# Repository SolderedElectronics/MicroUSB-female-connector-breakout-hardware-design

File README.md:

# MicroUSB female connector breakout Hardware Design

## About the Product

|  |
| :----------------------------------------------------------: |
| [Buy MicroUSB female connector breakout](https://www.solde.red/333010) |

The MicroUSB is still everywhere around us, even though it’s slowly being replaced with USB Type-C. We’re sure you wanted to add it to your electronics projects. We did, too, that’s why we added the MicroUSB female connector breakout board to our roster!

The Micro B USB connector’s GND, ID, D+, D-, and VCC pins are broken out to the plated through-holes.

---

## Repository Contents

This repository contains all design files for MicroUSB female connector breakout, organized as follows:

- **`CAD` folder**: Contains KiCAD design files, including:
  - Schematics
  - PCB layout
  - Panel PCB layout
  - Source 3D files in Fusion360, if any
  - All files are sorted by version with a detailed change log.
- **`OUTPUTS` folder**: Includes all production-ready files, such as:
  - Bill of Materials (BOM) and interactive BOM (iBOM)
  - PDF versions of schematics
  - 3D `.step` file of the board
  - 3D-printable models
  - Gerber files for PCB manufacturing
  - Image of the pinout of the board
  - Product image
  - Compliance, legal and generic sales documents

Refer to the `Change Log` in the CAD folder for details about updates between versions.

---

## Learn More About the Product

Beyond the repository, explore the following resources:

### Soldered Verify

The **Soldered Verify** system ensures every board you purchase from Soldered is fully functional. It also provides access to exclusive test data for your product. To get started, find the unique Soldered Verify ID on your product's packaging and enter the ID on the [Soldered Verify page](https://soldered.com/verify/) to access test results and additional product details.

### Soldered Community

Soldered Community is your go-to place for technical support. Our engineers track and answer all questions posted there, and it’s a great space for the maker community. Get answers to your questions and solutions for your challenges at [Soldered Community](https://soldered.com/community).

### solde.red

solde.red is an ultimate URL shortener and information hub. Access it by typing solde.red/ followed by your product SKU, e.g., [solde.red/333000](https://solde.red/333000), to find getting-started guides, datasheets, open-source hardware and software files, certifications, images, pinouts, and more. Read more about the shortener [here](https://solde.red/info/).

---

## Contributing

Contributions are welcome! Here’s how you can get involved:

- Submit pull requests to enhance the design or fix issues.
- Report bugs or problems by opening an issue.

We encourage community collaboration to make this product even better.

---

## About Soldered

[Soldered for Makers](https://soldered.com) specializes in designing and manufacturing electronic products tailored for enthusiasts, ranging from hobbyists to professionals. Our portfolio includes electronic boards, sensors, and actuators that are widely utilized in fields such as microelectronics, mechatronics, robotics, programming, and IoT. Every product we offer is designed in-house and built upon open-source hardware and software platforms. Proudly certified and manufactured within the European Union, our catalog likely includes the product you need for your project.

We complement these products with comprehensive tutorials and manuals, product descriptions, schematics, programming codes, and project examples. Our round-the-clock [customer and technical support](https://soldered.com/community) is available for all our products, irrespective of the sales channel. Soldered’s success and services reflect our maker community’s unwavering [trust](https://www.trustpilot.com/review/soldered.com), for which we are deeply grateful. Join our community and create using Soldered products.

---

## License

All Soldered open-source hardware (OSH) is under The TAPR Open Hardware License. Read more in the LICENSE file located in this repository.

**Disclaimer:**

No warranty - all designs in this repository are distributed in the hope that they will be useful, but without any warranty. They are provided "AS IS", therefore without warranty of any kind, either expressed or implied. The entire quality and performance of what you do with the contents of this repository are your responsibility. In no event Soldered Electronics will be liable for your damages, or losses, including any general, special, incidental, or consequential damage arising out of the use or inability to use the contents of this repository. 

---

## Have fun!

Thank you for your support from your fellow makers at Soldered Electronics.

Happy Making!

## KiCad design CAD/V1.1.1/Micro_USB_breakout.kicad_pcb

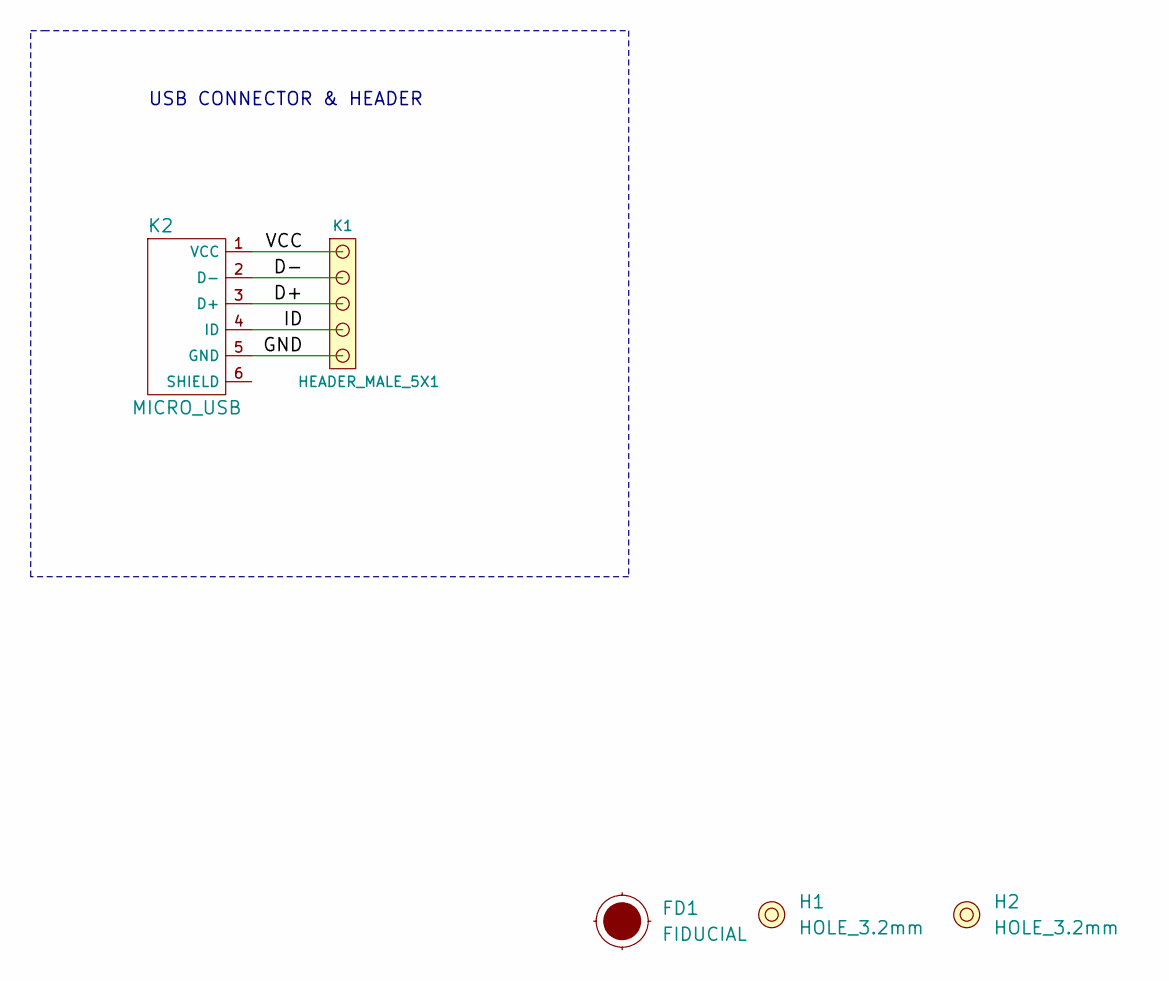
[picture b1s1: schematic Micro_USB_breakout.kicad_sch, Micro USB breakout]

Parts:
FD1: FIDUCIAL; FIDUCIAL_23
H1, H2: HOLE_3.2mm
K1: HEADER_MALE_5X1
K2: MICRO_USB

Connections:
/D+: K1.3, K2.3 (D+)
/D-: K1.4, K2.2 (D-)
/GND: K1.1, K2.5 (GND)
/ID: K1.2, K2.4 (ID)
/VCC: K1.5, K2.1 (VCC)

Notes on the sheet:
USB CONNECTOR & HEADER

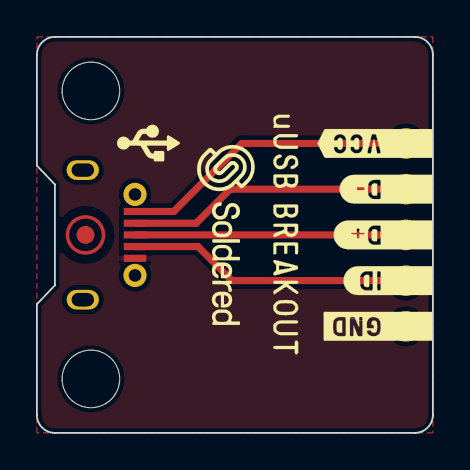
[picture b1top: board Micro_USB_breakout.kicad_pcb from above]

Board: 2 copper layers, 22.0 x 22.0 mm, 5 parts (1 on the bottom side), 5 nets.

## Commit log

2022-08-06 Updating open source files.
